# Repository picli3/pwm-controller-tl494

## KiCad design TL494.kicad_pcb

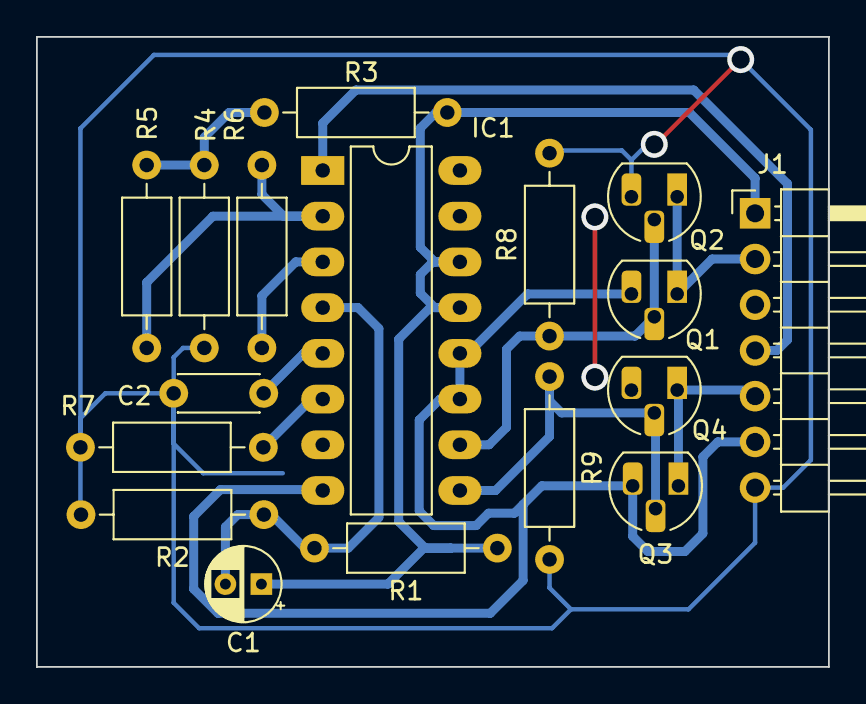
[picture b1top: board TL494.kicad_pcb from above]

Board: 2 copper layers, 44.0 x 35.0 mm, 17 parts (0 on the bottom side), 14 nets.

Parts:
C1: 2.5uF; CP_Radial_D4.0mm_P2.00mm
C2: 1nF; C_Disc_D4.3mm_W1.9mm_P5.00mm
IC1: TL494; DIP-16_W7.62mm_LongPads
J1: Conn_01x03; PinHeader_1x07_P2.54mm_Horizontal
Q1, Q3: 2N3904; TO-92L_HandSolder
Q2, Q4: 2N3906; TO-92L_HandSolder
R1: 9.1K; R_Axial_DIN0207_L6.3mm_D2.5mm_P10.16mm_Horizontal
R2, R8, R9: 1K; R_Axial_DIN0207_L6.3mm_D2.5mm_P10.16mm_Horizontal
R3, R4: 10K; R_Axial_DIN0207_L6.3mm_D2.5mm_P10.16mm_Horizontal
R5: 510; R_Axial_DIN0207_L6.3mm_D2.5mm_P10.16mm_Horizontal
R6: 51K; R_Axial_DIN0207_L6.3mm_D2.5mm_P10.16mm_Horizontal
R7: 50K; R_Axial_DIN0207_L6.3mm_D2.5mm_P10.16mm_Horizontal

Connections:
+12VA: IC1.8 (C1), IC1.11 (C2), IC1.12 (VCC), J1.6, Q1.3 (C), Q3.3 (C)
/E1: IC1.9 (E1), Q3.2 (B), Q4.2 (B), R9.1
/E2: IC1.10 (E2), Q1.2 (B), Q2.2 (B), R8.1
/OUT_A: J1.5, Q3.1 (E), Q4.1 (E)
/OUT_B: J1.2, Q1.1 (E), Q2.1 (E)
/VREF: C1.1, IC1.13 (OUTC), IC1.14 (VREF), J1.1, R1.1, R3.1
/V_sense: IC1.1 (+I1), J1.4
GNDA: C2.2, IC1.7 (GND), J1.7, Q2.3 (C), Q4.3 (C), R2.2, R4.2, R7.2, R8.2, R9.2
unnamed: IC1.2 (-I1), R5.1, R6.1
unnamed: IC1.3 (COMP), R6.2
unnamed: C2.1, IC1.5 (CT)
unnamed: C1.2, IC1.4 (DTC), R1.2, R2.1
unnamed: IC1.6 (RT), R7.1
unnamed: R3.2, R4.1, R5.2

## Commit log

2023-04-02 subiendo modulo PWM
2023-04-07 actualizando documentos de fabricacion
2023-04-07 volviendo a modificar porq me olvide de algo
